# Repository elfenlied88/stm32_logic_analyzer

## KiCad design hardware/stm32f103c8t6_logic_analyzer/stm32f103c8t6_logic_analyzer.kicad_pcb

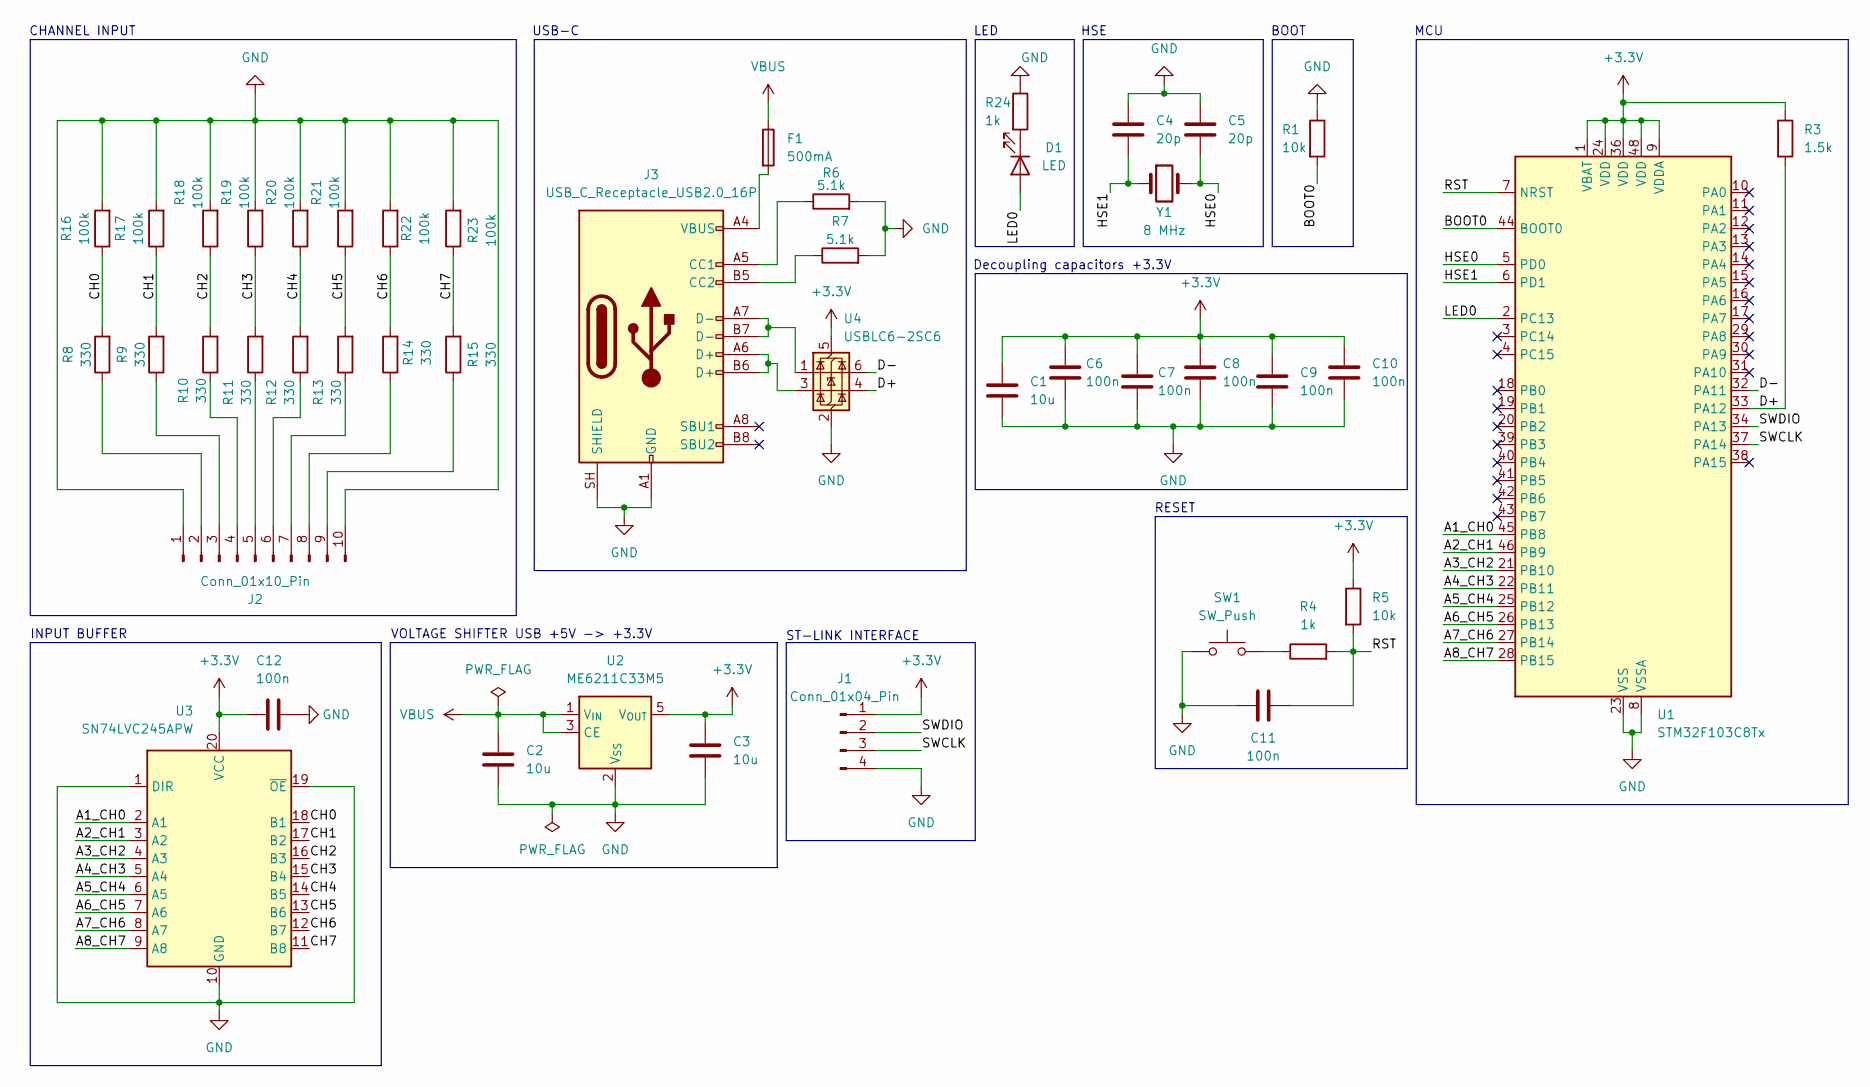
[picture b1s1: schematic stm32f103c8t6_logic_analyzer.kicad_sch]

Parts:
C1, C2, C3: 10u; C_0805_2012Metric
C4, C5: 20p; C_0603_1608Metric
C6, C7, C8, C9, C10, C11, C12: 100n; C_0603_1608Metric
D1: LED; LED_0603_1608Metric
F1: 500mA; Fuse_0805_2012Metric
J1: Conn_01x04_Pin; PinHeader_1x04_P2.54mm_Vertical
J2: Conn_01x10_Pin; PinHeader_1x10_P2.54mm_Vertical
J3: USB_C_Receptacle_USB2.0_16P; USB_C_Receptacle_HRO_TYPE-C-31-M-12
R1, R5: 10k; R_0603_1608Metric
R3: 1.5k; R_0603_1608Metric
R4, R24: 1k; R_0603_1608Metric
R6, R7: 5.1k; R_0603_1608Metric
R8, R9, R10, R11, R12, R13, R14, R15: 330; R_0603_1608Metric
R16, R17, R18, R19, R20, R21, R22, R23: 100k; R_0603_1608Metric
SW1: SW_Push; SW_SPST_B3U-1000P
U1: STM32F103C8Tx; LQFP-48_7x7mm_P0.5mm
U2: ME6211C33M5; SOT-23-5
U3: SN74LVC245APW; TSSOP-20_4.4x6.5mm_P0.65mm
U4: USBLC6-2SC6; SOT-23-6
Y1: 8 MHz; Crystal_SMD_Abracon_ABM3-2Pin_5.0x3.2mm

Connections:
+3.3V: C1.1, C3.1, C6.1, C7.1, C8.1, C9.1, C10.1, C12.1, J1.1, R3.1, R5.1, U1.1 (VBAT), U1.9 (VDDA), U1.24 (VDD), U1.36 (VDD), U1.48 (VDD), U2.5 (V_{OUT}), U3.20 (VCC), U4.5 (VBUS)
/A1_CH0: U1.45 (PB8), U3.2 (A1)
/A2_CH1: U1.46 (PB9), U3.3 (A2)
/A3_CH2: U1.21 (PB10), U3.4 (A3)
/A4_CH3: U1.22 (PB11), U3.5 (A4)
/A5_CH4: U1.25 (PB12), U3.6 (A5)
/A6_CH5: U1.26 (PB13), U3.7 (A6)
/A7_CH6: U1.27 (PB14), U3.8 (A7)
/A8_CH7: U1.28 (PB15), U3.9 (A8)
/BOOT0: R1.2, U1.44 (BOOT0)
/CH0: R8.2, R16.1, U3.18 (B1)
/CH1: R9.2, R17.1, U3.17 (B2)
/CH2: R10.2, R18.1, U3.16 (B3)
/CH3: R11.2, R19.1, U3.15 (B4)
/CH4: R12.2, R20.1, U3.14 (B5)
/CH5: R13.2, R21.1, U3.13 (B6)
/CH6: R14.2, R22.1, U3.12 (B7)
/CH7: R15.2, R23.1, U3.11 (B8)
/D+: R3.2, U1.33 (PA12), U4.4 (I/O2)
/D-: U1.32 (PA11), U4.6 (I/O1)
/HSE0: C5.2, U1.5 (PD0), Y1.2
/HSE1: C4.2, U1.6 (PD1), Y1.1
/LED0: D1.2 (A), U1.2 (PC13)
/RST: C11.1, R4.2, R5.2, U1.7 (NRST)
/SWCLK: J1.3, U1.37 (PA14)
/SWDIO: J1.2, U1.34 (PA13)
GND: C1.2, C2.2, C3.2, C4.1, C5.1, C6.2, C7.2, C8.2, C9.2, C10.2, C11.2, C12.2, J1.4, J2.1, J2.10, J3.A1 (GND), J3.A12 (GND), J3.B1 (GND), J3.B12 (GND), J3.SH (SHIELD), R1.1, R6.2, R7.2, R16.2, R17.2, R18.2, R19.2, R20.2, R21.2, R22.2, R23.2, R24.1, SW1.1, U1.8 (VSSA), U1.23 (VSS), U1.35 (VSS), U1.47 (VSS), U2.2 (V_{SS}), U3.1 (DIR), U3.10 (GND), U3.19 (~OE), U4.2 (GND)
unnamed: D1.1 (K), R24.2
unnamed: F1.2, J3.A4 (VBUS), J3.A9 (VBUS), J3.B4 (VBUS), J3.B9 (VBUS)
unnamed: J2.2, R8.1
unnamed: J2.3, R9.1
unnamed: J2.4, R10.1
unnamed: J2.5, R11.1
unnamed: J2.6, R12.1
unnamed: J2.7, R13.1
unnamed: J2.8, R14.1
unnamed: J2.9, R15.1
unnamed: J3.A5 (CC1), R6.1
unnamed: J3.B5 (CC2), R7.1
unnamed: J3.A6 (D+), J3.B6 (D+), U4.3 (I/O2)
unnamed: J3.A7 (D-), J3.B7 (D-), U4.1 (I/O1)
unnamed: R4.1, SW1.2
VBUS: C2.1, F1.1, U2.1 (V_{IN}), U2.3 (CE)

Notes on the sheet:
LED
HSE
VOLTAGE SHIFTER USB +5V -> +3.3V
CHANNEL INPUT
MCU
INPUT BUFFER
USB-C
ST-LINK INTERFACE
RESET
Decoupling capacitors +3.3V
BOOT

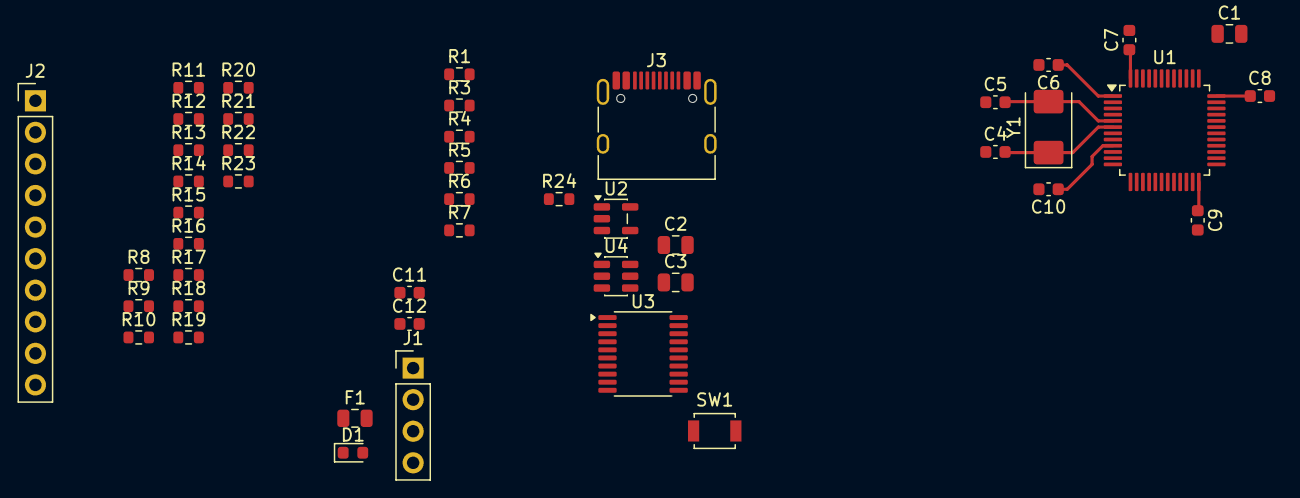
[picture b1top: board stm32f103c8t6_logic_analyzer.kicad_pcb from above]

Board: 2 copper layers, 46 parts (0 on the bottom side), 43 nets.

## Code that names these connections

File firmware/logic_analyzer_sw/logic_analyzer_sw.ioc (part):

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Mcu.Name=STM32F103C(8-B)Tx
Mcu.Package=LQFP48
Mcu.UserName=STM32F103C8Tx
PA11.Mode=Device
PA11.Signal=USB_DM
PA12.Mode=Device
PA12.Signal=USB_DP
PA13.Mode=Serial_Wire
PA13.Signal=SYS_JTMS-SWDIO
PA14.Mode=Serial_Wire
PA14.Signal=SYS_JTCK-SWCLK
PB10.Signal=GPIO_Input
PB11.Signal=GPIO_Input
PB12.Signal=GPIO_Input
PB13.Signal=GPIO_Input
PB14.Signal=GPIO_Input
PB15.Signal=GPIO_Input
PB8.Signal=GPIO_Input
PB9.Signal=GPIO_Input
PC13-TAMPER-RTC.Signal=GPIO_Output
PD0-OSC_IN.Mode=HSE-External-Oscillator
PD0-OSC_IN.Signal=RCC_OSC_IN
PD1-OSC_OUT.Mode=HSE-External-Oscillator
PD1-OSC_OUT.Signal=RCC_OSC_OUT
RCC.SYSCLKFreq_VALUE=72000000
RCC.SYSCLKSource=RCC_SYSCLKSOURCE_PLLCLK
board=custom
